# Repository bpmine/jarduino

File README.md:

# Jarduino

Le Jarduino est un ensemble de systèmes pour l'arrosage du jardin.

Il comporte les sous-ensembles suivants:
- Gestion des goutteurs
- Gestion des cuves
- Gestion des oyas

Le principal objectif du projet est de s'amuser tout en mettant à profit les compétences acquises lors d'une réponse à un cahier des charges pour un projet professionnel qui n'a finalement pas abouti.

La réalisation inclue des cartes électroniques conçues sur mesure, du logiciel, quelques petites pièces mécaniques et bien d'autres éléments....

## Illustrations (photos)

## Gestion des goutteurs

### Aux origines...

Le système de goutteurs est le "Jarduino" historique, mis en place assez rapidement (en 2019 ?) pour partir en vacances sans s'occuper de l'arrosage.

Il a fonctionné presque jusqu'au bout. Le panneau solaire s'est retourné (vent?), et sans énergie, il s'est arrêté...

Depuis 2019, chaque année, le Jarduino fonctionne toujours en se perfectionnant. Il a compté jusqu'à une cinquantaine de goutteurs en 2022.

### Jarduino 2

Ce Jarduino est un peu plus sérieux, basé sur de vraies cartes électroniques et non plus sur des platines de prototypage.

Il a été prévu en deux étapes:
- Tout d'abord une version simple basée sur un arduino Nano et une RTC;
- ensuite, une connexion Wifi via un ESP01 et la liaison série / modbus.

Il a fonctionné sans difficultés. Mais le module Wifi n'est toujours pas prêt (en 2024)...

#### Principe

Une cuve permet de stoker de l'eau. Un boîtier de contrôle alimenté par un panneau solaire avec une batterie pilote une pompe qui allimente les goutteurs.
Le boîtier pilote jusqu'à deux pompes et peut être programmé à une heure donnée pour une durée d'arrosage souhaitée.

Voir ici la description détaillée: [Système de goutteurs](./goutteurs)

## Gestion des cuves

Plusieurs cuves récupèrent l'eau de pluie et permettent d'approvisioner les systèmes d'arrosage automatiques.
Un système de pompes contrôlables à distance permet de gérer leur niveau.

Voir ici la description détaillée: [Gestion des cuves](./cuves)

## Gestion des OYAs

Le système permet de diffuser de l'eau aux plantes par la terre grâce à des sortes de petites jarres en argile appellées OYAs.
Ce dispositif a été déployé après les goutteurs, en 2023. Il remplace petit à petit le système de goutteurs.

Voir ici la description détaillée: [Gestion des OYAs](./oyas)

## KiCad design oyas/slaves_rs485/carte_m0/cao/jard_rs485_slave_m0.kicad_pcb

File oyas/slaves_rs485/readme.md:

# Esclaves RS485

Ce sont des cartes esclaves permettant de piloter pompes et oyas.

## Types de carte

### Carte_arduino

Design initial à base de modules arduino nano.
Gestion des pompes et des oyas avec la même carte.
Les premières cartes comportaient un module RS485 indépendant. Il a ensuite été intégré sur la carte mère.
Ces cartes sont alimentées par le régulateur du module nano.
Il y'a eu plusieurs versions de cette "première" carte. 

Cette carte existe depuis 2023. Elle a donc déjà un long historique. Elle fonctionnait avec un vieux protocole qui a été remplacé dans la dernière version de logiciel.

### Carte AT328

Seule l'alimentation à découpage provient d'un module extérieur. Tout le reste a été intégré en composant CMS ou tranversants (connecteurs).
Il n'y a plus de capteur de température DHT22.
Il n'y a qu'un seul gros bornier pour accueillir les fils du bus.
Elle peut gérer soit une pompe, soir un oya.
Le logiciel utilise le arduinocore (compatible arduino).

### Carte MSP430

Même principe que la carte à base de AT328 mais ne peut gérer qu'un oya.
Il était prévu de pouvoir à terme gérer également la pompe avec cette carte.

Mais 2 MSP430 sur 3 achetés sur aliexpress s'avèrent impossible à programmer! Il semblent qu'il aient été bloqués par logiciels. Peut-être le vendeur a-t-il mélangé des MSP430 corrects aau milieu d'une série bloquée? 

Le choix s'expliquait par ma connaissance de ce micro suite à son utilisation dans l'un de mes projets profesionnels dans les années 2000. 

Même si j'adore ce micro, ce n'était pas une bonne idée:
- L'environnement IAR gratuit n'est plus dispo en téléchargement pour <32k
- Le MSP430F1232 est devenu obsolète

### Carte M0 (avec ATSAMD21G18A-A)

Suite aux problèmes rencontrés par les MSP430 achetés sur aliexpress, je décide d'abandonner définitivement le MSP430.

Je change également de critère pour choisir le cpu:
- Avoir une clock interne performante et assez précise pour ne pas nécessiter de quartz
- Compatible avec l'un des environnements que je connais
- Suffisament de périphériques et de broches pour pouvoir l'utiliser sur d'autres projets
- ...

Tant pis si je sors de l'Arduino... retour aux sources !

Le choix est le ATSAMD21G18A. La soudure à la main est assez délicate mais j'y arrive.

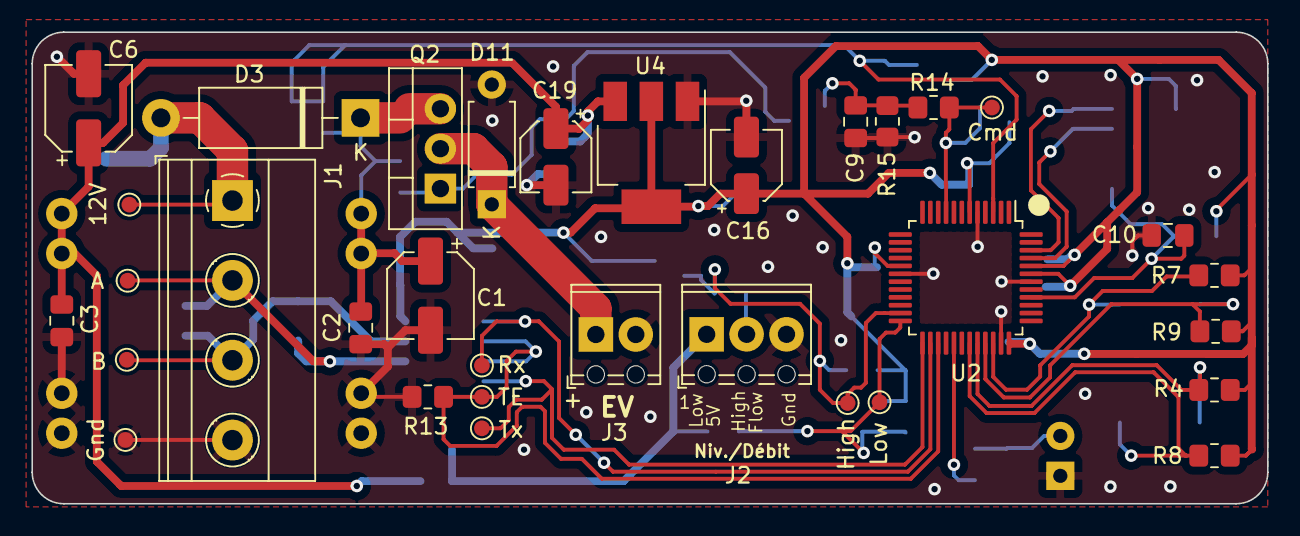
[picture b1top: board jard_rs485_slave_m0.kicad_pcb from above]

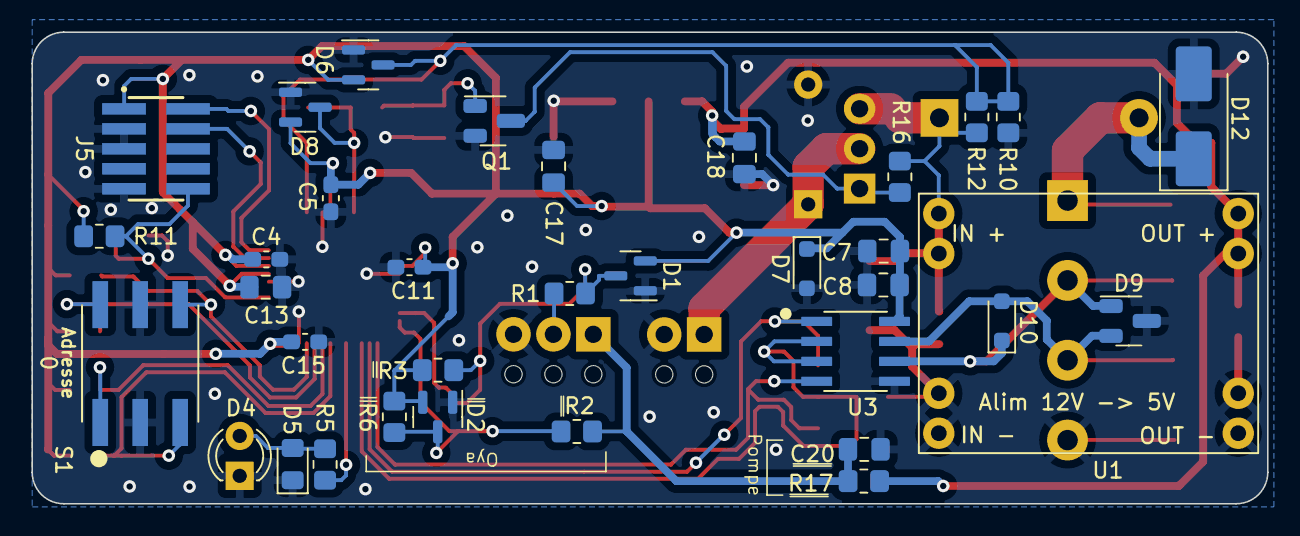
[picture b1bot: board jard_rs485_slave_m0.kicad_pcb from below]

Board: 2 copper layers, 78.6 x 30.0 mm, 68 parts (35 on the bottom side), 28 nets.

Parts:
C1: 33µF; CP_Elec_5x5.9
C2, C8, C9, C10, C17, C20: 100nF; C_0805_2012Metric_Pad1.18x1.45mm_HandSolder
C3, C18: 1nF; C_0805_2012Metric_Pad1.18x1.45mm_HandSolder
C4, C5, C11, C15: 100nF; C_0603_1608Metric_Pad1.08x0.95mm_HandSolder
C6: 10µF; CP_Elec_5x5.9
C7: 10µF; C_0805_2012Metric_Pad1.18x1.45mm_HandSolder
C13: 1µF; C_0805_2012Metric_Pad1.18x1.45mm_HandSolder
C16, C19: 10µF; CP_Elec_4x5.4
D1, D2, D6, D8: BAV99; SOT-23
D3: SR560; D_DO-15_P12.70mm_Horizontal
D4: LED; LED_D3.0mm_FlatTop
D5: LED; LED_0805_2012Metric_Pad1.15x1.40mm_HandSolder
D7, D10: SD12_SOD323; BPC_D_SOD-323_HandSoldering
D9: SM712_SOT23; BPC_SOT-23-3_HandSoldering
D11: 1N4007G; D_A-405_P7.62mm_Horizontal
D12: SMBJ18A; D_SMB_Handsoldering
J1: POWER; TerminalBlock_Phoenix_MKDS-1,5-4-5.08_1x04_P5.08mm_Horizont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
J2: Niveaux/Débit; TerminalBlock_Phoenix_MPT-0,5-3-2.54_1x03_P2.54mm_Horizontal
J3: EV1; TerminalBlock_Phoenix_MPT-0,5-2-2.54_1x02_P2.54mm_Horizontal
J5: BPC_PRG_FTSH-105-01-L-DV-K_1; BPC_SAMTEC_FTSH-105-01-L-DV-K
Q1: BPC_FMMT38C; BPC_SOT-23-3_HandSoldering
Q2: P03P4L-04; TO-220-3_Vertical
R1, R2, R14: 1k; R_0805_2012Metric_Pad1.20x1.40mm_HandSolder
R3, R4, R6, R7, R8, R9, R12, R13, R15, R16: 100k; R_0805_2012Metric_Pad1.20x1.40mm_HandSolder
R5: 220; R_0805_2012Metric_Pad1.20x1.40mm_HandSolder
R10: 27k; R_0805_2012Metric_Pad1.20x1.40mm_HandSolder
R11: 10k; R_0805_2012Metric_Pad1.20x1.40mm_HandSolder
R17: 0; R_0805_2012Metric_Pad1.20x1.40mm_HandSolder
S1: RDS-16S-74385-SMT; BPC_RDS-16S-74385-SMT
TP1: 12V; TestPoint_Pad_D1.0mm
TP2: Gnd; TestPoint_Pad_D1.0mm
TP3: High; TestPoint_Pad_D1.0mm
TP4: Low; TestPoint_Pad_D1.0mm
TP5: Rx; TestPoint_Pad_D1.0mm
TP6: Tx; TestPoint_Pad_D1.0mm
TP7: TE; TestPoint_Pad_D1.0mm
TP8: Cmd; TestPoint_Pad_D1.0mm
TP9: B; TestPoint_Pad_D1.0mm
TP10: A; TestPoint_Pad_D1.0mm
U1: BPC_Alim5V
U2: ATSAMD21G18A-A; TQFP-48_7x7mm_P0.5mm
U3: MAX3485; BPC_MAX485E_SOIC127P600X175-8N
U4: AP1117-15; BPC_SOT-223-3_TabPin2

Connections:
+3.3V: C4.1, C5.2, C7.1, C8.2, C11.2, C13.1, C15.1, C16.1, C17.1, D1.2 (A), D2.2 (A), D6.2 (A), D7.1 (A1), D8.2 (A), J5.01, R3.2, R4.2, R6.2, R7.2, R8.2, R9.2, R11.1, U2.6 (VDDANA), U2.17 (VDDIO), U2.36 (VDDIO), U2.43 (VDDCORE), U2.44 (VDDIN), U3.8 (VCC), U4.2 (VO)
+5V: C3.1, C6.1, C18.1, C19.1, R17.1, U1.7 (OUT+), U1.8 (OUT+), U4.3 (VI)
A1: R4.1, S1.1, U2.32 (PA23)
A2: R7.1, S1.2, U2.34 (PA25)
A3: R8.1, S1.4, U2.31 (PA22)
A4: R9.1, S1.8, U2.33 (PA24)
BUS_A: D9.1 (A1), D10.1 (A1), J1.2, TP10.1, U3.6 (A)
BUS_B: D9.2 (A2), D10.2 (A2), J1.3, TP9.1, U3.7 (B)
CMD_EV1: D8.3 (K), R14.1, TP8.1, U2.9 (PA04)
GND: C1.2, C2.2, C3.2, C4.2, C5.1, C6.2, C7.2, C8.1, C9.2, C10.1, C11.1, C13.2, C15.2, C16.2, C17.2, C18.2, C19.2, C20.1, D1.1 (K), D2.1 (K), D4.1 (K), D5.1 (K), D6.1 (K), D7.2 (A2), D8.1 (K), D9.3 (common), D11.2 (A), D12.2 (A2), J1.4, J2.3, J3.2, J5.03, J5.05, J5.09, Q1.2 (E), R10.1, R13.2, R15.2, S1.C_1 (C), S1.C_2 (C), TP2.1, U1.3 (IN-), U1.4 (IN-), U1.5 (OUT-), U1.6 (OUT-), U2.5 (GNDANA), U2.18 (GND), U2.35 (GND), U2.42 (GND), U3.5 (GND), U4.1 (GND)
LED: R5.1, U2.29 (PA20)
LVL_HIGH_FLOW: D1.3 (K), R1.2, R3.1, TP3.1, U2.23 (PA14)
LVL_LOW: D2.3 (K), R2.2, R6.1, TP4.1, U2.24 (PA15)
unnamed: D4.2 (A), D5.2 (A), R5.2
unnamed: D11.1 (K), J3.1, Q2.2 (D)
unnamed: D3.2 (A), D12.1 (A1), J1.1, TP1.1
unnamed: C20.2, J2.1, R2.1, R17.2
unnamed: J2.2, R1.1
unnamed: C9.1, Q1.1 (B), R14.2, R15.1
unnamed: Q1.3 (C), Q2.1 (G), R16.2
POWER_12V: C1.1, C2.1, D3.1 (K), Q2.3 (S), R12.2, R16.1, U1.1 (IN+), U1.2 (IN+)
POW_MES: D6.3 (K), R10.2, R12.1, U2.3 (PA02)
RX: TP5.1, U2.26 (PA17), U3.1 (RO)
SWCLK: J5.04, U2.45 (PA30)
SWDIO: J5.02, U2.46 (PA31)
TX: TP6.1, U2.25 (PA16), U3.4 (DI)
TX_EN: R13.1, TP7.1, U2.27 (PA18), U3.2 (~RE), U3.3 (DE)
/RESET: C10.2, J5.10, R11.2, U2.40 (~RESET)

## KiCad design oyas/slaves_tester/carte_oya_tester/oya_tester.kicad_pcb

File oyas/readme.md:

# Système de gestion des OYAs

## Présentation

Le but du système de remplissage automatique des OYAs est de pouvoir s'absenter pendant les vacances tout en laissant les OYAs se gérer tous seuls.

### Oyas

Les OYAs sont des sortes de pots en argile enterrés utilisés depuis des millénaires pour distribuer de l'eau à des cultures.

On remplit régulièrement ces pots. Grâce à leur porosité, l'eau se diffuse à travers l'OYAs au fur et à mesure où les racines des plantes assèchent la terre à proximité.

- Ils évitent les pertes d'eau par évaporation
- ne mouillent pas les feuilles des plantes
- ne mouille pas le sol en surface
- évitent le stress hydrique
- permettent de faire des économies d'eau

### Principe de fonctionnement

Des cuves récupèrent l'eau de pluie. A partir de ces cuves, un système comportant une pompe et plusieurs électrovannes permet de remplir les OYAs.

Le système rempli chaque OYA jusqu'au maximum ou bien selon le programme souhaité. La stratégie de remplissage est entièrement programmable.

## Description de nos réseaux d'OYAs

Notre installation comporte actuellement (en 2025) trois réseaux d'OYAs reliés chacun à une cuve et à son alimentation électrique autonome.

## Réseau A : Barbecue

C'est le plus ancien (mise en service en 2023). Il comporte à ce jour:

- 1 maître
- 1 pompe
- 7 OYAs
- 1 EV pour remplir un réservoir d'appoint

 Caractéristique | Description
-- | --
Nombre de nœuds | 10
Longueur | environ 30 m
Volume cuve | 520 L
Capacité totale des Oyas | 64 L (4x10 + 3x8 + cuve de 100L non gérée actuellement)
Alimentation | 1 Panneau solaire 120W + 2 Batteries 12V au plomb

La cuve et l'alimentation 12V déservent à la fois le système d'OYAs et un système de gestion de goutteurs alimenté par une petite pompe.

Ce réseau est à la fois composé de cartes électroniques  esclaves de "première génération" Rev Ax et de cartes récentes (Rev Gx produites en 2024).

Très bon retour sur le fonctionnement pendant l'été 2023. 
Excellent retour aussi en 2024.

A noter cependant la fragilité des électrovannes. Pour fonctionner correctement, il est nécessaire d'avoir une eau d'arrivée sans impureté. En effet, celle ci peut se déposer entre le corps et la membrane de l'électrovanne et bloquer cette dernière en position ouverte. Le tuyau 10mm transparent génère des algues qui sèchent pendant l'hiver lors de l'entreposage du système. Lors de la remise en service au printemps 2023, des morceaux d'algue de l'année précédente se sont détachées et sont venues perturber le fonctionnement des électrovannes.

## Réseau B : Réduit

- 1 maître
- 1 pompe
- 12 OYAs (dont 4 ajoutés en 2025)

Caractéristique | Description
-- | --
Nombre de nœuds | 13
Longueur | environ 35 m
Volume cuve | 520 L
Capacité totale des Oyas | 100 L (2x10 + 10x8) 
Alimentation | 1 Panneau solaire 120W + 2 Batteries 12V au plomb

Mis en service en 2024. Etendu en 2025.

## Réseau C : Nord (Derrière la maison)

- 1 maître
- 1 pompe
- 6 OYAs

Caractéristique | Description
-- | --
Nombre de nœuds | 7
Longueur | environ 15 m
Volume cuve | 300 L
Capacité totale des Oyas | 48 L (6x8) 
Alimentation | ? (A définir)

Mis en service en 2025.

## Pilotage par Wifi

Les deux maîtres des OYAs sont accessibles par Wifi.

On peut prendre le contrôle et consulter en temps réel le niveau d'eau dans chaque OYA.
On peut également paramétrer le fonctionnement du système (heures et stratégies de remplissages, ...).

Ci-dessous une capture d'un monitoring du 14/08/2024:

Durant nos vacances, les données sont également acheminées vers un cloud et mémorisées dans une base de données.
On peut ainsi voir évoluer les niveaux d'eau.

## Composants d'un réseau d'OYAs

### Réseau/Tuyau

Chaque système OYAs est composé d'un module maître et de plusieurs modules esclaves reliés entre eux par un réseau RS485 et un tuyau 12mm.

Le câble réseau comporte une alimentation 12V et les fils A et B du RS485.

Le réseau possède deux résistances de terminaison de 120 Ohms aux deux extrémités. Il est également polarisé côté maître par une pull up et une pull down de 220 Ohms (Valeur encore susceptible de bouger).

Pour trouver les bonnes valeurs et étant donné la mauvaise qualité de câble utilisé, il faut effectuer des mesures de signal au bout du bus et vérifier que les tensions au repos de A et de B sont conformes à la norme RS485. 

__NB:__ Le dispositif de la photo ci-dessus contient une résistance de 128 Ohm. On appelle ça un "bouchon" !! (d'où le bouchon de liège...)

## Modules électronique de pilotage

### Module Pompe

Le module pompe contient une carte esclave RS485 en configuration "pompe".

Connecteurs:
- connecteur 4 voies bus RS485 + alim
- connecteur pompe
- connecteur débitmètre

Ce module est placé en sortie de cuve pour pomper l'eau et donner une certaine pression dans le tuyau. La pompe est nécessaire pour assurer un débit constant quelque soit le niveau d'eau dans la cuve et quelle que soit la hauteur relative entre la cuve et les différents OYAs.

Il faut aussi noter qu'une pression minimale est nécessaire pour ouvrir une électrovanne (voir ces caractéristiques).

Le schéma et le pcb de la carte sont ici: [Carte esclave RS485](./slaves_rs485/hard)

Plusieurs versions ont été réalisées, compatibles entre-elles. A ce jour le système est composé de façon hétérogène par ces différentes versions.

Version | Date | Description
-- | -- | --
Rev Ax | 2023 | Version initiale avec modules (forme en L)
Rev Bx | 2023 | Correction RX/TX inversé
Rev Dx | 2024 | Version sans module (tout intégré en CMS)
Rev Ex | 2024 | Avec modules (petite carte)
Rev Gx | 2024 | MAX485 en CMS (petite carte)

Le logiciel est ici: [Logiciel esclave RS485](.\slaves_rs485\src)

### Module Oya

Le module OYA contient une carte esclave RS485 en configuration "OYA".

Connecteurs:
- connecteur 4 voies bus RS485 + alim
- connecteur électrovanne
- connecteur niveaux

Il contient également une électrovanne 12V et un capteur de niveau.

Ce module est placé sur chaque OYA.

Le capteur de niveau comporte deux flotteurs qui ferment un contact en position basse.

### Module Maître

Le maître des OYAs permet de commander une pompe et plusieurs électrovannes pour remplir des OYAs.

## Protocole réseau (RS485)

Le réseau est de type RS485. Il comporte un maître et plusieurs esclaves. Chaque esclave a une adresse unique (de 1 à 14 ou 1 à E en hexadécimal).

Seul le maître peut initier une communication. Un seul esclave peut répondre à une trame émise par le maître.

Types de messages du maître:

- Trame Commandes
- Trame Ping
- Trame Sync

Types de réponses d'un esclave:

- Trame Pompe
- Trame Oya
- Trame Pong

La communication se fait par cycles. Chaque cycle se termine par une trame Sync.

Durant un cycle, le maître envoie autant de trames __*"Commandes"*__ qu'il y'a d'esclaves configurés. Chaque trame __*"Commandes"*__ comporte un appel destiné à un esclave en particulier. Seul l'esclave appelé peut répondre avec l'une des deux trames __*"Oya"*__ ou __*"Pompe"*__.

Après un __*"Sync"*__, le maître doit impérativement attendre un temps minimum avant d'initier un nouveau cycle. Cela permet aux esclaves d'effectuer des traitements.

Pour plus de détails, voir

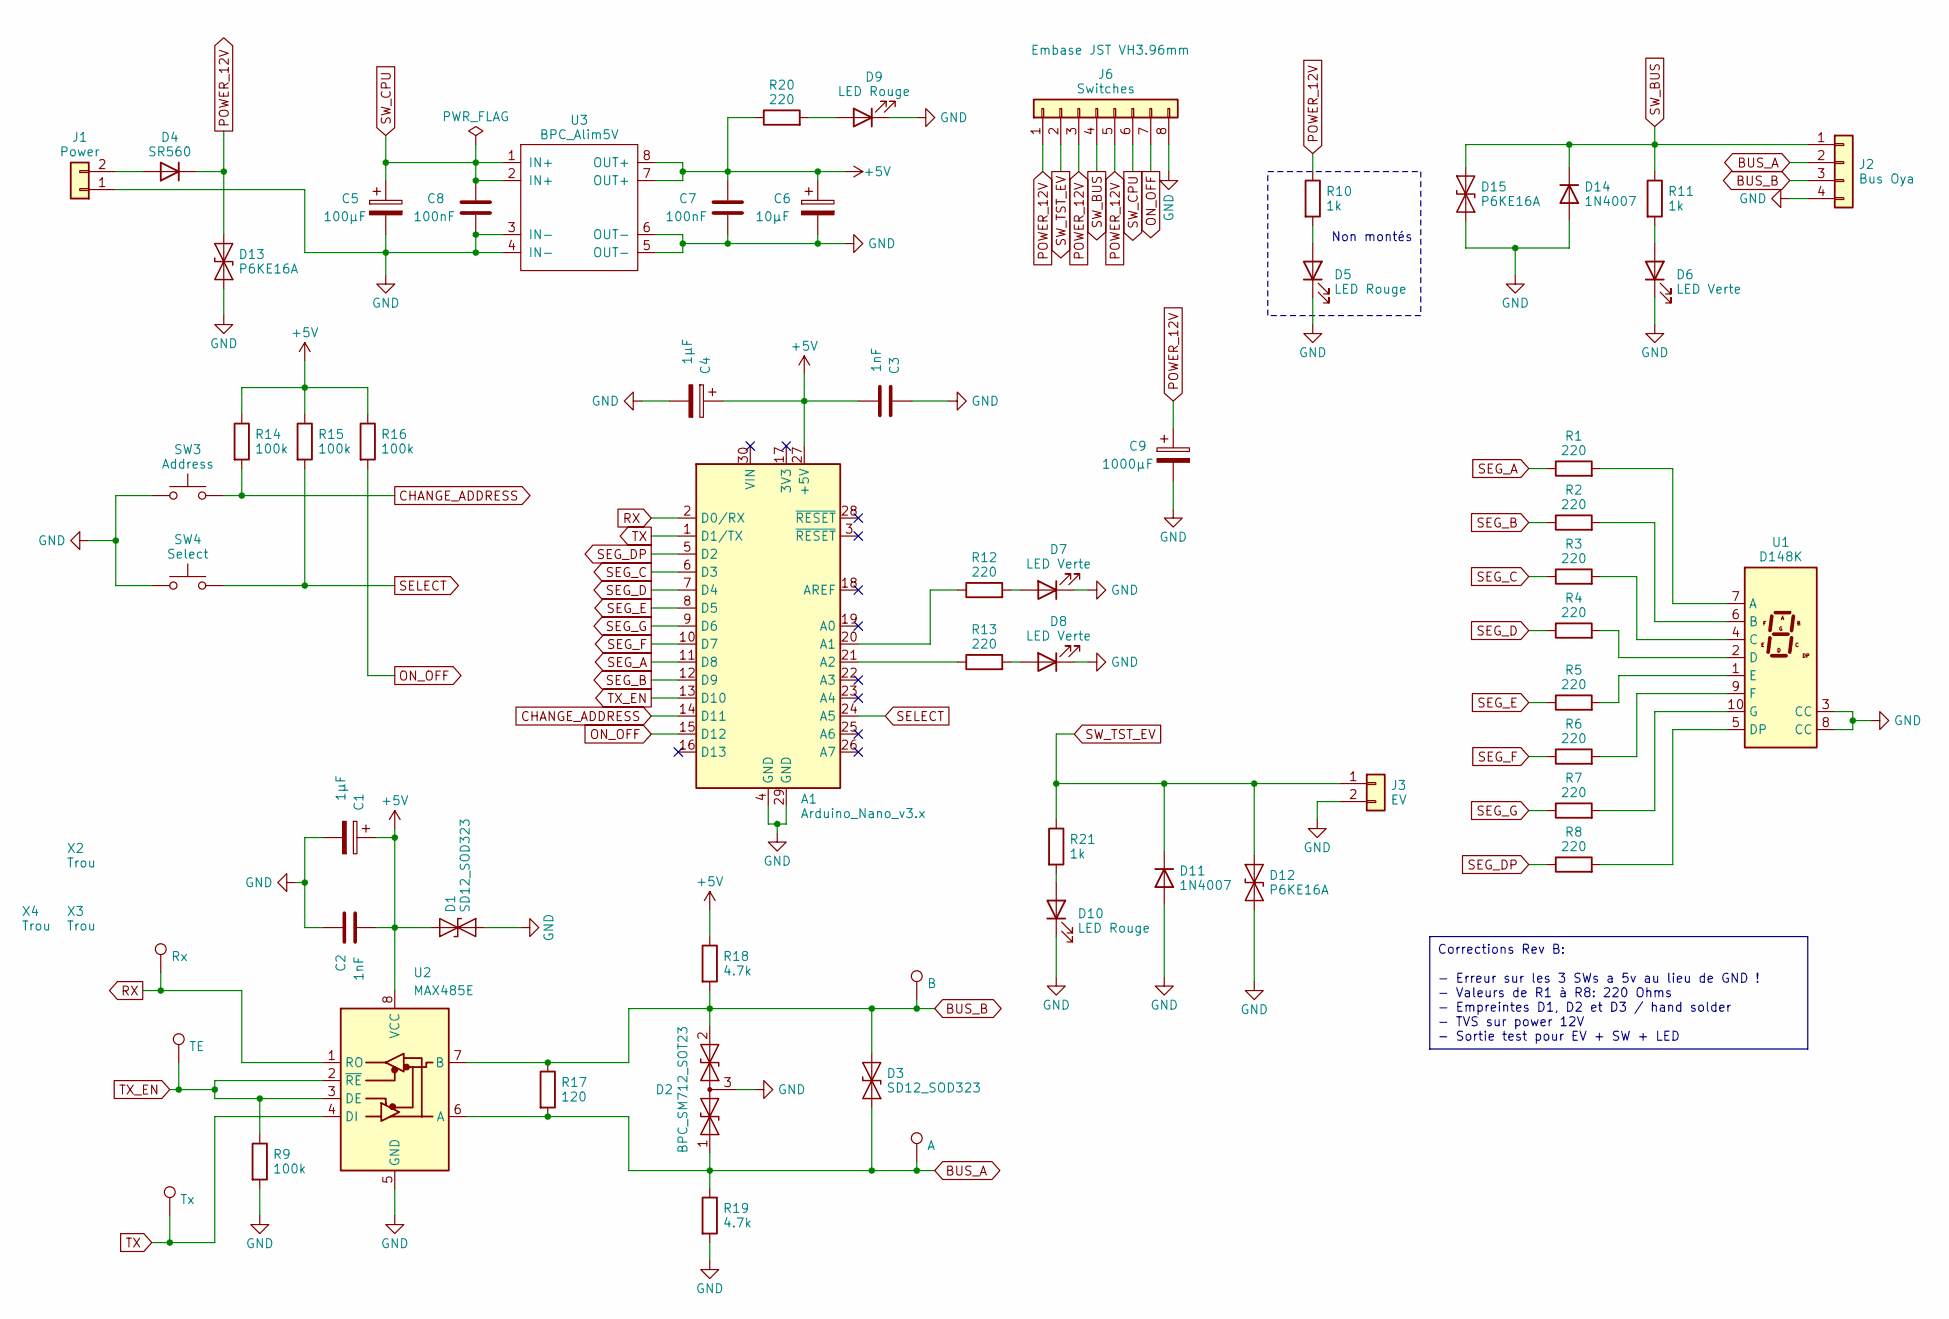
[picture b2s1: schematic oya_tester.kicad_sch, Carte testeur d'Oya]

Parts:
A1: Arduino_Nano_v3.x; BPC_Arduino_Nano
C1, C4: 1µF; C_0805_2012Metric_Pad1.18x1.45mm_HandSolder
C2, C3: 1nF; C_0805_2012Metric_Pad1.18x1.45mm_HandSolder
C5: 100µF; CP_Radial_D8.0mm_P3.50mm
C6: 10µF; CP_Radial_D5.0mm_P2.50mm
C7, C8: 100nF; C_0805_2012Metric_Pad1.18x1.45mm_HandSolder
C9: 1000µF; CP_Radial_D16.0mm_P7.50mm
D1, D3: SD12_SOD323; BPC_D_SOD-323_HandSoldering
D2: BPC_SM712_SOT23; BPC_SOT-23-3_HandSoldering
D4: SR560; D_DO-15_P12.70mm_Horizontal
D5, D9, D10: LED Rouge; LED_D3.0mm_FlatTop
D6, D7, D8: LED Verte; LED_D3.0mm_FlatTop
D11, D14: 1N4007; D_DO-41_SOD81_P3.81mm_Vertical_KathodeUp
D12, D15: P6KE16A; D_DO-15_P3.81mm_Vertical_KathodeUp
D13: P6KE16A; D_DO-15_P10.16mm_Horizontal
J1: Power; TerminalBlock_Phoenix_MKDS-1,5-2-5.08_1x02_P5.08mm_Horizont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
J2: Bus Oya; TerminalBlock_Phoenix_MKDS-1,5-4-5.08_1x04_P5.08mm_Horizont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
J3: EV; TerminalBlock_Phoenix_MKDS-1,5-2-5.08_1x02_P5.08mm_Horizont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
J6: Switches; JST_VH_B8P-VH-B_1x08_P3.96mm_Vertical
R1, R2, R3, R4, R5, R6, R7, R8, R12, R13, R20: 220; R_0805_2012Metric_Pad1.20x1.40mm_HandSolder
R9, R14, R15, R16: 100k; R_0805_2012Metric_Pad1.20x1.40mm_HandSolder
R10, R11, R21: 1k; R_0805_2012Metric_Pad1.20x1.40mm_HandSolder
R17: 120; R_Axial_DIN0204_L3.6mm_D1.6mm_P5.08mm_Horizontal
R18, R19: 4.7k; R_Axial_DIN0204_L3.6mm_D1.6mm_P5.08mm_Horizontal
SW3: Address; SW_PUSH_6mm
SW4: Select; SW_PUSH_6mm
TP1: Rx; TestPoint_Pad_D2.0mm
TP2: Tx; TestPoint_Pad_D2.0mm
TP3: TE; TestPoint_Pad_D2.0mm
TP4: B; TestPoint_Pad_D2.0mm
TP5: A; TestPoint_Pad_D2.0mm
U1: D148K; BPC_7SEG_D1X8K
U2: MAX485E; BPC_MAX485E_SOIC127P600X175-8N
U3: BPC_Alim5V
X2, X3, X4: Trou; BPC_Trou4mm_Fixation

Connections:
+5V: A1.27 (+5V), C1.1, C2.2, C3.2, C4.1, C6.1, C7.1, D1.1 (A1), R14.1, R15.1, R16.1, R18.1, R20.1, U2.8 (VCC), U3.7 (OUT+), U3.8 (OUT+)
BUS_A: D2.1 (A1), D3.1 (A1), J2.2, R17.2, R19.1, TP5.1, U2.6 (A)
BUS_B: D2.2 (A2), D3.2 (A2), J2.3, R17.1, R18.2, TP4.1, U2.7 (B)
CHANGE_ADDRESS: A1.14 (D11), R14.2, SW3.2
GND: A1.4 (GND), A1.29 (GND), C1.2, C2.1, C3.1, C4.2, C5.2, C6.2, C7.2, C8.2, C9.2, D1.2 (A2), D2.3 (common), D5.1 (K), D6.1 (K), D7.1 (K), D8.1 (K), D9.1 (K), D10.1 (K), D11.2 (A), D12.1 (A1), D13.1 (A1), D14.2 (A), D15.1 (A1), J1.1, J2.4, J3.2, J6.8, R9.2, R19.2, SW3.1, SW4.1, U1.3 (CC), U1.8 (CC), U2.5 (GND), U3.3 (IN-), U3.4 (IN-), U3.5 (OUT-), U3.6 (OUT-)
unnamed: A1.20 (A1), R12.1
unnamed: A1.21 (A2), R13.1
unnamed: D4.2 (A), J1.2
unnamed: D5.2 (A), R10.2
unnamed: D6.2 (A), R11.2
unnamed: D7.2 (A), R12.2
unnamed: D8.2 (A), R13.2
unnamed: D9.2 (A), R20.2
unnamed: D10.2 (A), R21.2
unnamed: R1.2, U1.7 (A)
unnamed: R2.2, U1.6 (B)
unnamed: R3.2, U1.4 (C)
unnamed: R4.2, U1.2 (D)
unnamed: R8.2, U1.5 (DP)
unnamed: R5.2, U1.1 (E)
unnamed: R6.2, U1.9 (F)
unnamed: R7.2, U1.10 (G)
ON_OFF: A1.15 (D12), J6.7, R16.2
POWER_12V: C9.1, D4.1 (K), D13.2 (A2), J6.1, J6.3, J6.5, R10.1
RX: A1.2 (D0/RX), TP1.1, U2.1 (RO)
SEG_A: A1.11 (D8), R1.1
SEG_B: A1.12 (D9), R2.1
SEG_C: A1.6 (D3), R3.1
SEG_D: A1.7 (D4), R4.1
SEG_DP: A1.5 (D2), R8.1
SEG_E: A1.8 (D5), R5.1
SEG_F: A1.10 (D7), R6.1
SEG_G: A1.9 (D6), R7.1
SELECT: A1.24 (A5), R15.2, SW4.2
SW_BUS: D14.1 (K), D15.2 (A2), J2.1, J6.4, R11.1
SW_CPU: C5.1, C8.1, J6.6, U3.1 (IN+), U3.2 (IN+)
SW_TST_EV: D11.1 (K), D12.2 (A2), J3.1, J6.2, R21.1
TX: A1.1 (D1/TX), TP2.1, U2.4 (DI)
TX_EN: A1.13 (D10), R9.1, TP3.1, U2.2 (~RE), U2.3 (DE)

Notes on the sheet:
Corrections Rev B: - Erreur sur les 3 SWs a 5v au lieu de GND ! - Valeurs de R1 à R8: 220 Ohms - Empreintes D1, D2 et D3 / hand solder - TVS sur power 12V - Sortie test pour EV + SW + LED
Non montés

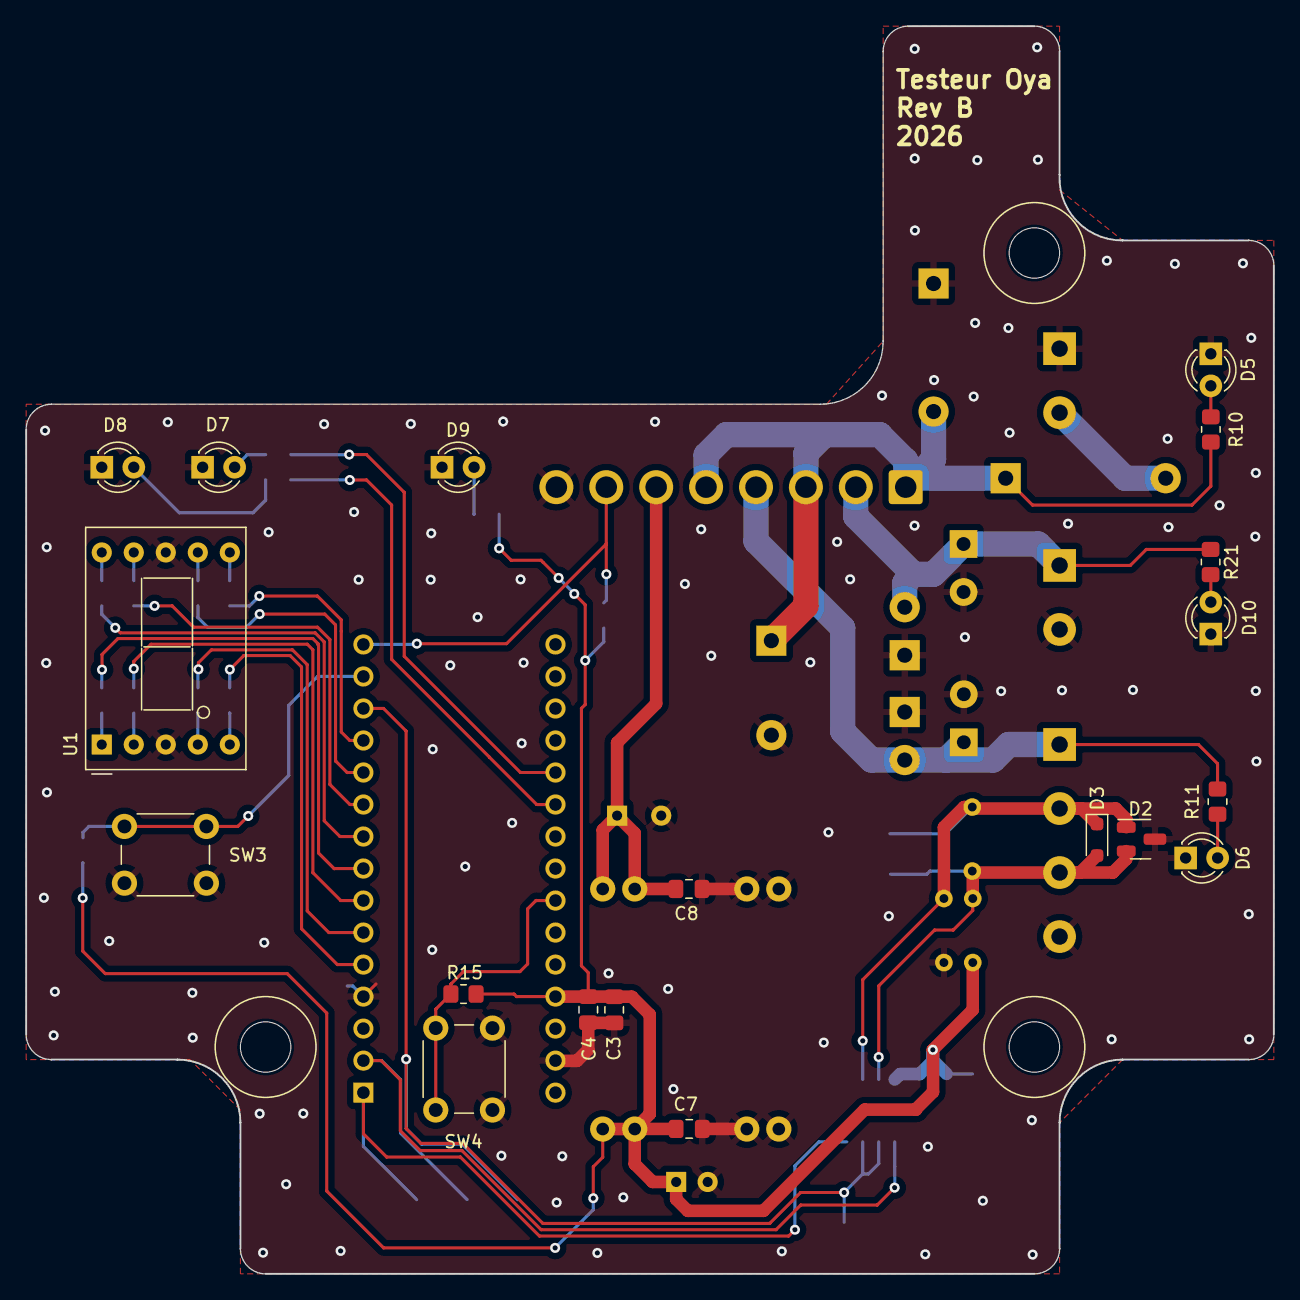
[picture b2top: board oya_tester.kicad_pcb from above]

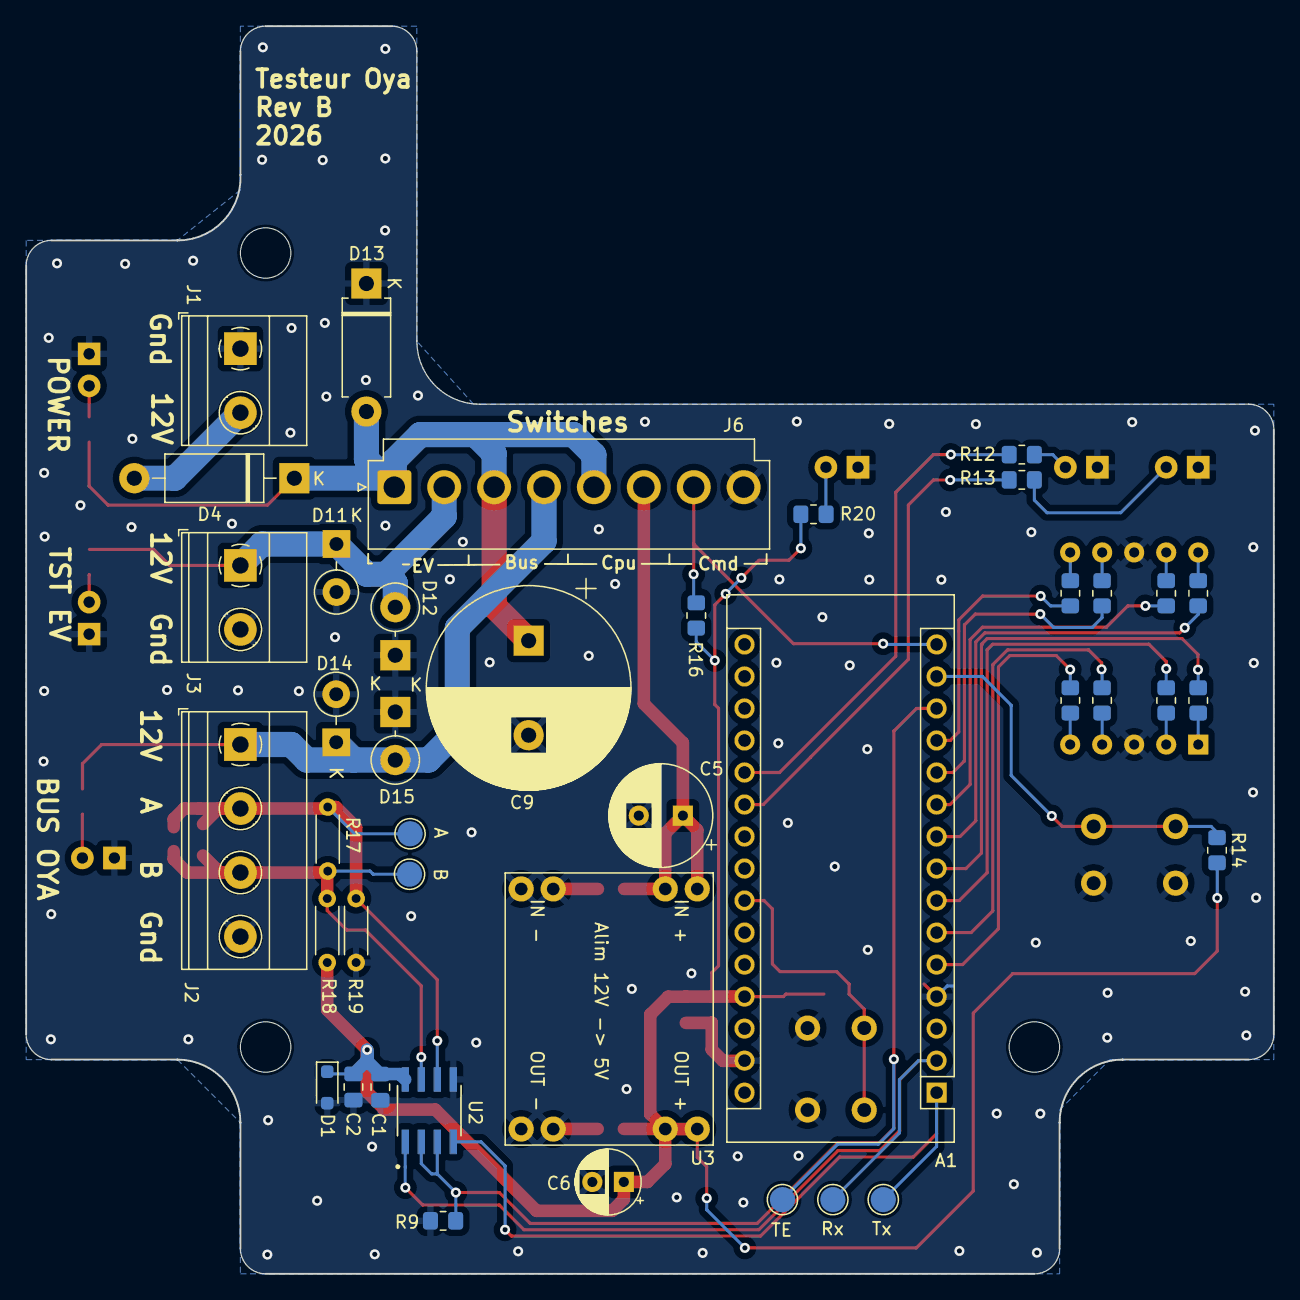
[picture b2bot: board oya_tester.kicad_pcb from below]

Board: 2 copper layers, 99.0 x 99.0 mm, 63 parts (41 on the bottom side), 39 nets.

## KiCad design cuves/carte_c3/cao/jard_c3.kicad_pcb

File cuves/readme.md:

# Cuves

Nous avons 4 cuves pour une capacité totale de 2200 L.

- Cuve principale de 1000 L
- cuve  "Paul" de 300 L
- cuve "Réduit" de 520 L
- cuve "Barbec" de 520 L

Deux cuves de 520 L et une de 300 L alimentent nos deux systèmes de remplissage automatique des OYAs.

Les cuves sont communicantes et un système permet de pomper l'eau de la cuve principale vers les autres. 

## Description des cuves

### Cuve principale (Main)

Cette cuve recueille l'eau du toit de la maison. D'une capacité de 1000 L, elle constitue la réserve principale.
Elle sert à alimenter la cuve "Paul" et aussi la cuve "Réduit" en cas de besoin.

Comme on peut le voir sur la troisième photo, une colonne PVC de 32mm est utilisée comme jauge de niveau.
Cette solution permet d'éviter de percer des trous dans la paroi de la cuve (comme pour les autres).

Trois capteurs à flotteur sont fixés sur cette colonne qui ensuite est remplie de résine pour rendre le tout étanche et durable:

A la base de la cuve, un système de 2 pompes (précédées de filtres) permet de déplacer l'eau vers les autres cuves (Paul et Réduit):

Le modèle de pompe utilisé est le AW500S 12V 5m 800L/H:

Pour la petite histoire, nous disposions avant 2023 à cet emplacement d'une cuve de moindre contenance.
Mal positionnée sur son support, un jour de pluie elle est tombée de tout son poids et BOOM !

Depuis, elle marche moins bien...

### Cuve Paul

La cuve "Paul" (de Paul) de 220 L permet d'alimenter un système de 6 oyas (en 2025). Anciennement, elle alimentait les derniers goutteurs pour des bacs de jardinage (5 bacs en 2024).

La détection de niveau est réalisée à l'aide de 3 capteurs avec flotteur montés sur la paroi de la cuve.

### Cuve Réduit

Cette cuve de 520 L alimente un système de remplisage d'OYAs et permet également d'alimenter la cuve Barbecue si besoin.

La détection de niveau est réalisée à l'aide de 3 capteurs avec flotteur montés sur la paroi de la cuve. 

Le système de capteurs a montré ses limites car des fuites sont apparus au bout d'un an d'utilisation au niveau de ces capteurs.
Pour pallier au problème, de la résine a été utilisée pour recouvrir la zone sensible autour des capteurs.

### Cuve Barbecue

Cette cuve de 520 L alimente un système de remplisage d'OYAs et un système de goutteurs.
La détection de niveau est réalisée à l'aide de 3 capteurs avec flotteur montés sur la paroi de la cuve. 

## Filtres imprimés en 3D

Les électrovannes utilisées pour les OYAs et le transfert de l'eau inter-cuves, les pompes et les goutteurs requièrent une eau parfaitement filtrée.
Si pour les goutteurs d'entrée 8mm, cela paraît évident, il faut savoir que c'est également nécessaire pour les électrovannes. En effet, de petits morceaux d'algues peuvent bloquer une électrovanne en position ouverte.

C'est la raison pour laquelle des filtres ont été ajoutés à plusieurs endroits sur le tuyau (Cuves Paul, Réduit et Barbecue).

### Filtre sortie vers tuyau 4mm/8mm

Une pièce a été conçue et imprimée pour filtrer directement sur le tuyau PVC de sortie des cuves.
Elle a été utilisée avant 2023 lorsque tous les systèmes d'arrosages étaient en version goutteurs.

Ce filtre permet de brancher un tuyau 4 mm vers le système de gouteurs. 
Trop fragile, une version similaire avec une sortie 8 mm a ensuite été imprimée.

### Pré-filtre intérieur

Pour filtrer de plus gros morceaux avant le tuyau de sortie, la pièce suivante est vissée à l'intérieur des cuves (Réduit et Barbecue).

## Modules Wifi pour commander les pompes

### Description

Le module de pompage comporte:
- 1 alimentation 12V;
- 1 sortie pompe de 12V/5A;
- 3 entrées de type interrupteur (actif à l'état bas) pour la détection du niveau de cuve.

### Carte Wifi IO

Deux versions de cartes ont été réalisées:
- Carte wemos
- carte C3

La première à base d'un Wemos D1 mini (ESP8266). Cette carte fonctionne depuis 2024. Son boitier est petit et cela pose un problème avec la condensation. En 2025, deux cartes étaient déjà oxydées car elles baignaient dans l'eau. les boitiers ne sont pas parfaitement étanches.
Le projet se trouve ici: [Carte wemos](./carte_wemos)

La carte C3 est basée sur un module ESP32 C3 mini. Elle est censée mieux fonctionner... Fabriquée en 2026, elle est placée dans une boîte de dérivation plus grosse pour éviter que la condensation atteigne la carte.
Le projet se trouve ici: [Carte C3](./carte_c3)

La carte wemos s'avère plus puissante niveau Wifi et porte un peu plus loin. Les cartes C3 un peu moins bonnes et dépendantes de leur module C3 (dispertion).
Malgré tout, les cartes C3 semblent fonctionner correctement.

### Protocole d'échange avec MQTT

## Serveur de contrôle

Le serveur comporte un broker MQTT pour centraliser les connexions des différents modules du système.

Un serveur reddis stocke tous les états, les réglages et les commandes des différentes applications.

Les applications sont les suivantes:
- Interraction avec les modules de pompage
- Publication des états sur les écrans
- Webservice pour exposer les services à des clients
- Automatisme de contrôle
- Logger

## Module d'affichage

Le module d'affichage comporte un écran, OLED.

Il permet de visualiser l'état des cuves et l'activité de pompage en temps réel.

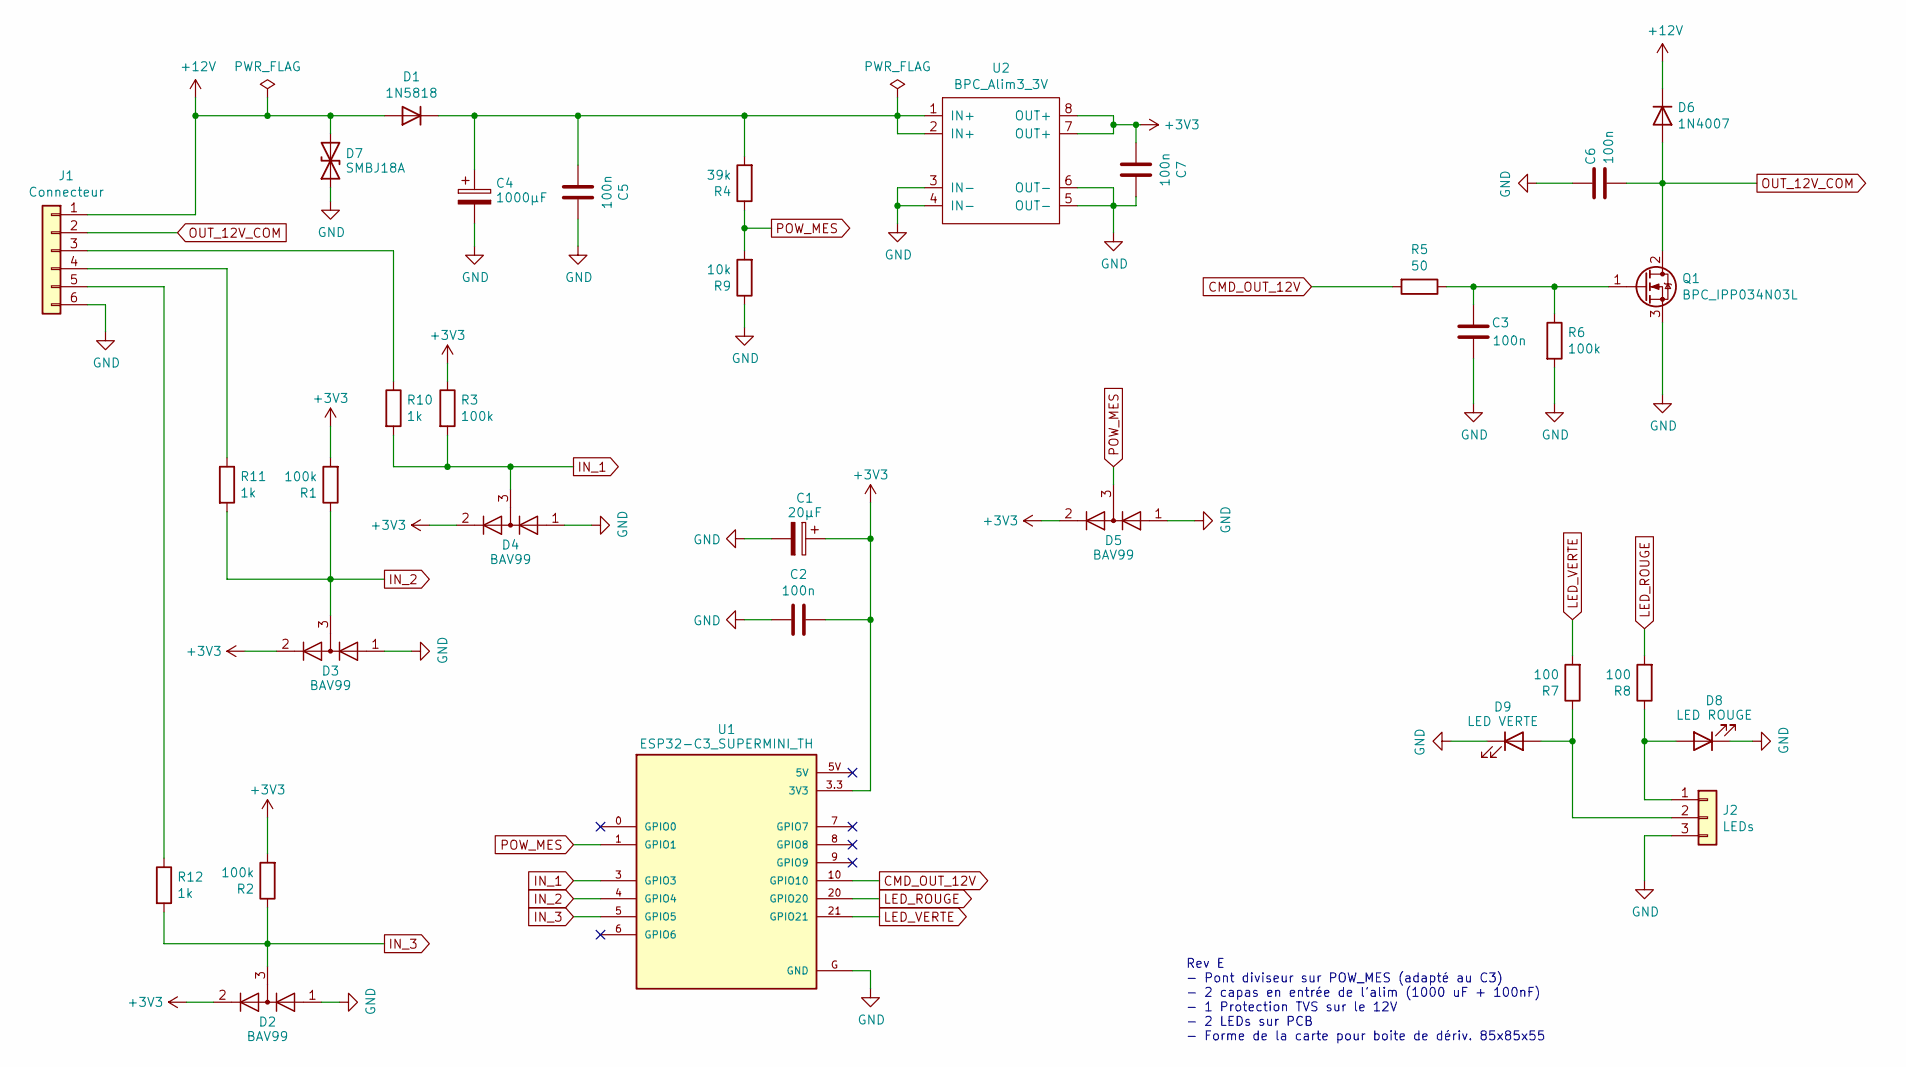
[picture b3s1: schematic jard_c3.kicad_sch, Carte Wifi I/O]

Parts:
C1: 20µF; C_Radial_D6.3mm_H7.0mm_P2.50mm
C2, C3, C5, C6, C7: 100n; C_0805_2012Metric_Pad1.18x1.45mm_HandSolder
C4: 1000µF; C_Radial_D16.0mm_H25.0mm_P7.50mm
D1: 1N5818; D_DO-41_SOD81_P10.16mm_Horizontal
D2, D3, D4, D5: BAV99; BPC_SOT-23-3_HandSoldering
D6: 1N4007; D_A-405_P2.54mm_Vertical_KathodeUp
D7: SMBJ18A; D_SMB_Handsoldering
D8: LED ROUGE; LED_D3.0mm
D9: LED VERTE; LED_D3.0mm
J1: Connecteur; TerminalBlock_Phoenix_MPT-0,5-6-2.54_1x06_P2.54mm_Horizontal
J2: LEDs; PinHeader_1x03_P2.54mm_Vertical
Q1: BPC_IPP034N03L; TO-220-3_Vertical
R1, R2, R3, R6: 100k; R_0805_2012Metric_Pad1.20x1.40mm_HandSolder
R4: 39k; R_0805_2012Metric_Pad1.20x1.40mm_HandSolder
R5: 50; R_0805_2012Metric_Pad1.20x1.40mm_HandSolder
R7, R8: 100; R_0805_2012Metric_Pad1.20x1.40mm_HandSolder
R9: 10k; R_0805_2012Metric_Pad1.20x1.40mm_HandSolder
R10, R11, R12: 1k; R_0805_2012Metric_Pad1.20x1.40mm_HandSolder
U1: ESP32-C3_SUPERMINI_TH; BPC_ESP32-C3_SUPERMINI
U2: BPC_Alim3_3V

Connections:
+3V3: C1.1, C2.1, C7.2, D2.2 (A), D3.2 (A), D4.2 (A), D5.2 (A), R1.2, R2.2, R3.1, U1.3.3 (3V3), U2.7 (OUT+), U2.8 (OUT+)
+12V: D1.2 (A), D6.1 (K), D7.2 (A2), J1.1
CMD_OUT_12V: R5.2, U1.10 (GPIO10)
GND: C1.2, C2.2, C3.2, C4.2, C5.1, C6.1, C7.1, D2.1 (K), D3.1 (K), D4.1 (K), D5.1 (K), D7.1 (A1), D8.1 (K), D9.1 (K), J1.6, J2.3, Q1.3 (S), R6.2, R9.1, U1.G (GND), U2.3 (IN-), U2.4 (IN-), U2.5 (OUT-), U2.6 (OUT-)
IN_1: D4.3 (K), R3.2, R10.2, U1.3 (GPIO3)
IN_2: D3.3 (K), R1.1, R11.2, U1.4 (GPIO4)
IN_3: D2.3 (K), R2.1, R12.2, U1.5 (GPIO5)
LED_ROUGE: R8.2, U1.20 (GPIO20)
LED_VERTE: R7.2, U1.21 (GPIO21)
unnamed: C4.1, C5.2, D1.1 (K), R4.2, U2.1 (IN+), U2.2 (IN+)
unnamed: D8.2 (A), J2.1, R8.1
unnamed: D9.2 (A), J2.2, R7.1
unnamed: J1.3, R10.1
unnamed: J1.4, R11.1
unnamed: J1.5, R12.1
unnamed: C3.1, Q1.1 (G), R5.1, R6.1
OUT_12V_COM: C6.2, D6.2 (A), J1.2, Q1.2 (D)
POW_MES: D5.3 (K), R4.1, R9.2, U1.1 (GPIO1)

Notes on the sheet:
Rev E - Pont diviseur sur POW_MES (adapté au C3) - 2 capas en entrée de l'alim (1000 uF + 100nF) - 1 Protection TVS sur le 12V - 2 LEDs sur PCB - Forme de la carte pour boite de dériv. 85x85x55
